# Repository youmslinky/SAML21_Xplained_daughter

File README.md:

# SAML21_Xplained_daughter
Atmel SAML21 Xplained daughter board for high altitude balloon payload

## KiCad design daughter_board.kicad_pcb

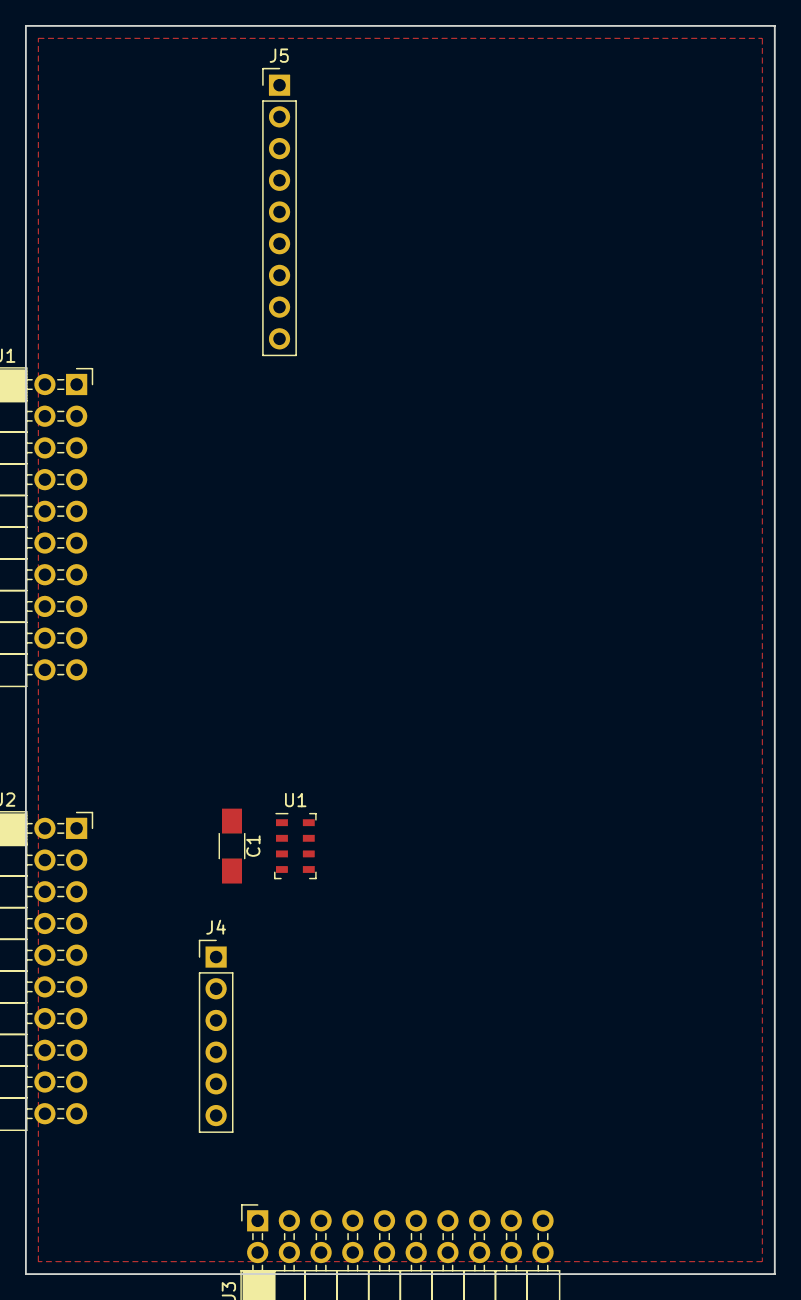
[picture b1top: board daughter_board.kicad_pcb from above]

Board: 2 copper layers, 60.0 x 100.0 mm, 7 parts (0 on the bottom side), 11 nets, no tracks yet.

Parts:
C1: 100nF; C_1206_HandSoldering
J1, J2, J3: Xplained_Pro_Extension_Header_2x10; Socket_Strip_Angled_2x10_Pitch2.54mm
J4: OpenLog_01x06; Socket_Strip_Straight_1x06_Pitch2.54mm
J5: ultimate_gps_header_1x9; Socket_Strip_Straight_1x09_Pitch2.54mm
U1: ms5611; LGA-8_3x5mm_Pitch1.25mm

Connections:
+3V3: C1.1, J1.20, J2.20, J3.20, J4.4, J5.2, U1.1, U1.2
/PA02: J1.10, J5.6
/PB06: J1.5, J5.8
/PB07: J1.6, J5.1
GND: C1.2, J1.2, J1.19, J2.2, J2.19, J3.2, J3.19, J4.5, J5.3, U1.3, U1.4, U1.5
GPS_RX: J1.14, J5.4
GPS_TX: J1.13, J5.5
TWI_SCL: J1.12, J2.12, J3.12, U1.8
TWI_SDA: J1.11, J2.11, J3.11, U1.7
openlog_RX: J2.14, J4.2
openlog_TX: J2.13, J4.3

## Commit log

2018-03-23 Add KiCAD .gitignore
    template gitignore for kicad
2018-03-23 Put gitignore in proper place
2018-03-23 Add all current project files
2018-03-23 Add library files
2018-03-23 Add preliminary footprint associations
2018-04-06 enlarge connector
2018-04-06 add grounds
2018-04-06 unknown?
    I'm not sure what this file change is
2018-04-10 Align ms5611 schematic pins to grid
2018-04-10 Make text on connectors readable
2018-04-11 Wire ms5611
    ms5611 wired for twi interface with address 0x76
2018-04-11 Add ultimate gps schematic symbol
2018-04-11 Add ultimate gps header
    only ground and 3.3V connected
2018-04-11 Hookup ultimate gps header
2018-04-11 Add library documentation file
2018-04-11 Add openlogger header to library
2018-04-11 Fix pins on expansion header schematic symbol
2018-04-11 Change uart global labels, add pin labels
    pin labels for actual saml21 IC pins
2018-04-11 Add openlogger header to schematic
2018-04-11 Re-assign footprint to ms5611
    footprint assignment got removed when ms5611 schematic symbol was removed and placed in again, this fixes that
2018-04-11 Assign pcb footprints
    capacitor, 2 headers
2018-04-11 Add custom footprint to footprint library
    expansion headers anchored in the center in order to align to xplained board
2018-04-11 Include jdk footprint library in project
2018-04-11 Start pcb layout
    position 3 main expansion headers
2018-04-13 Add library for Xbee schematic symbols
2018-04-13 Add Xbee footprint
    through hole footprint
2018-04-13 Add Xbee header to schematic
2018-04-13 Edit XBee header to include spi mode pin functions
2018-04-13 Add Xbee header and connect spi pins
2018-04-17 Label spi pins, add XBee reset button, add decoupling capacitors
2018-04-17 Add XBee attention pin
2018-04-17 ignore library cache file
